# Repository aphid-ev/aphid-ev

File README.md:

# Aphid EV

Everything that goes into the electric conversion of a classic VW Beetle:
documentation, wiring, ECU hardware and firmware, and the desktop tooling to
manage it.

The documentation site at <https://bladlus.se> is built from [`site/`](site/)
and is the single source of truth for the project. READMEs in this repository
only say what a directory is and how to build it.

## Layout

| Path | What |
| --- | --- |
| [`site/`](site/) | Blog and wiki for bladlus.se, built with [aphid](https://aphid.lhelge.se) |
| [`wiring/`](wiring/) | Vehicle schematics and harness drawings, built with [wirebug](https://github.com/LHelge/wirebug) |
| [`crates/`](crates/) | Shared `no_std` Rust crates used by firmware and host code |
| [`ecus/`](ecus/) | One directory per ECU: KiCad hardware and Rust firmware side by side |
| [`apps/`](apps/) | Desktop application for managing the ECUs over CAN |
| [`tools/`](tools/) | Small host-side CLIs used by the build |

aphid and wirebug are developed in their own repositories; this repository
only uses them.

## Working in the repository

All tasks go through [`just`](https://just.systems). CI runs the same recipes.

```sh
just                  # list every recipe, including per-component modules
just host ci          # format, lint and test the host workspace
just vcm build        # build one ECU's firmware
just vcm export       # export one ECU's schematics for the site
just site serve       # live-reload the site
just docs             # generate all artifacts and build the site
just ci               # everything CI runs
```

Required tools: a Rust toolchain via rustup, `just`, `aphid`, `wirebug`,
KiCad 10 (`kicad-cli`) and `probe-rs` for flashing. `just install-aphid` and
`just install-wirebug` install the versions CI uses.

## Rust workspaces

The root `Cargo.toml` is the host workspace: everything that runs on a desktop,
plus the shared crates so their tests run on the host. Each firmware is its own
small workspace with its own target, linker script, profiles and lock file, and
depends on the shared crates by path.

## Releases

Components are versioned and tagged separately: `<component>-fw-vX.Y.Z` for
firmware, `<component>-hw-revX` for board revisions and `manager-vX.Y.Z` for
the desktop app.

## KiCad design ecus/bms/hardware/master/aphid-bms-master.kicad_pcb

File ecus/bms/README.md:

# BMS

Battery management system: one master and one slave board per battery module.

- `hardware/master/` — KiCad project for the master board.
- `hardware/slave/` — KiCad project for the slave board. It has no firmware.
- `firmware/` — embassy firmware for the master, a standalone cargo workspace.

Recipes: `just bms build | check | flash | erc | drc | export | ci`. The
hardware recipes cover both boards.

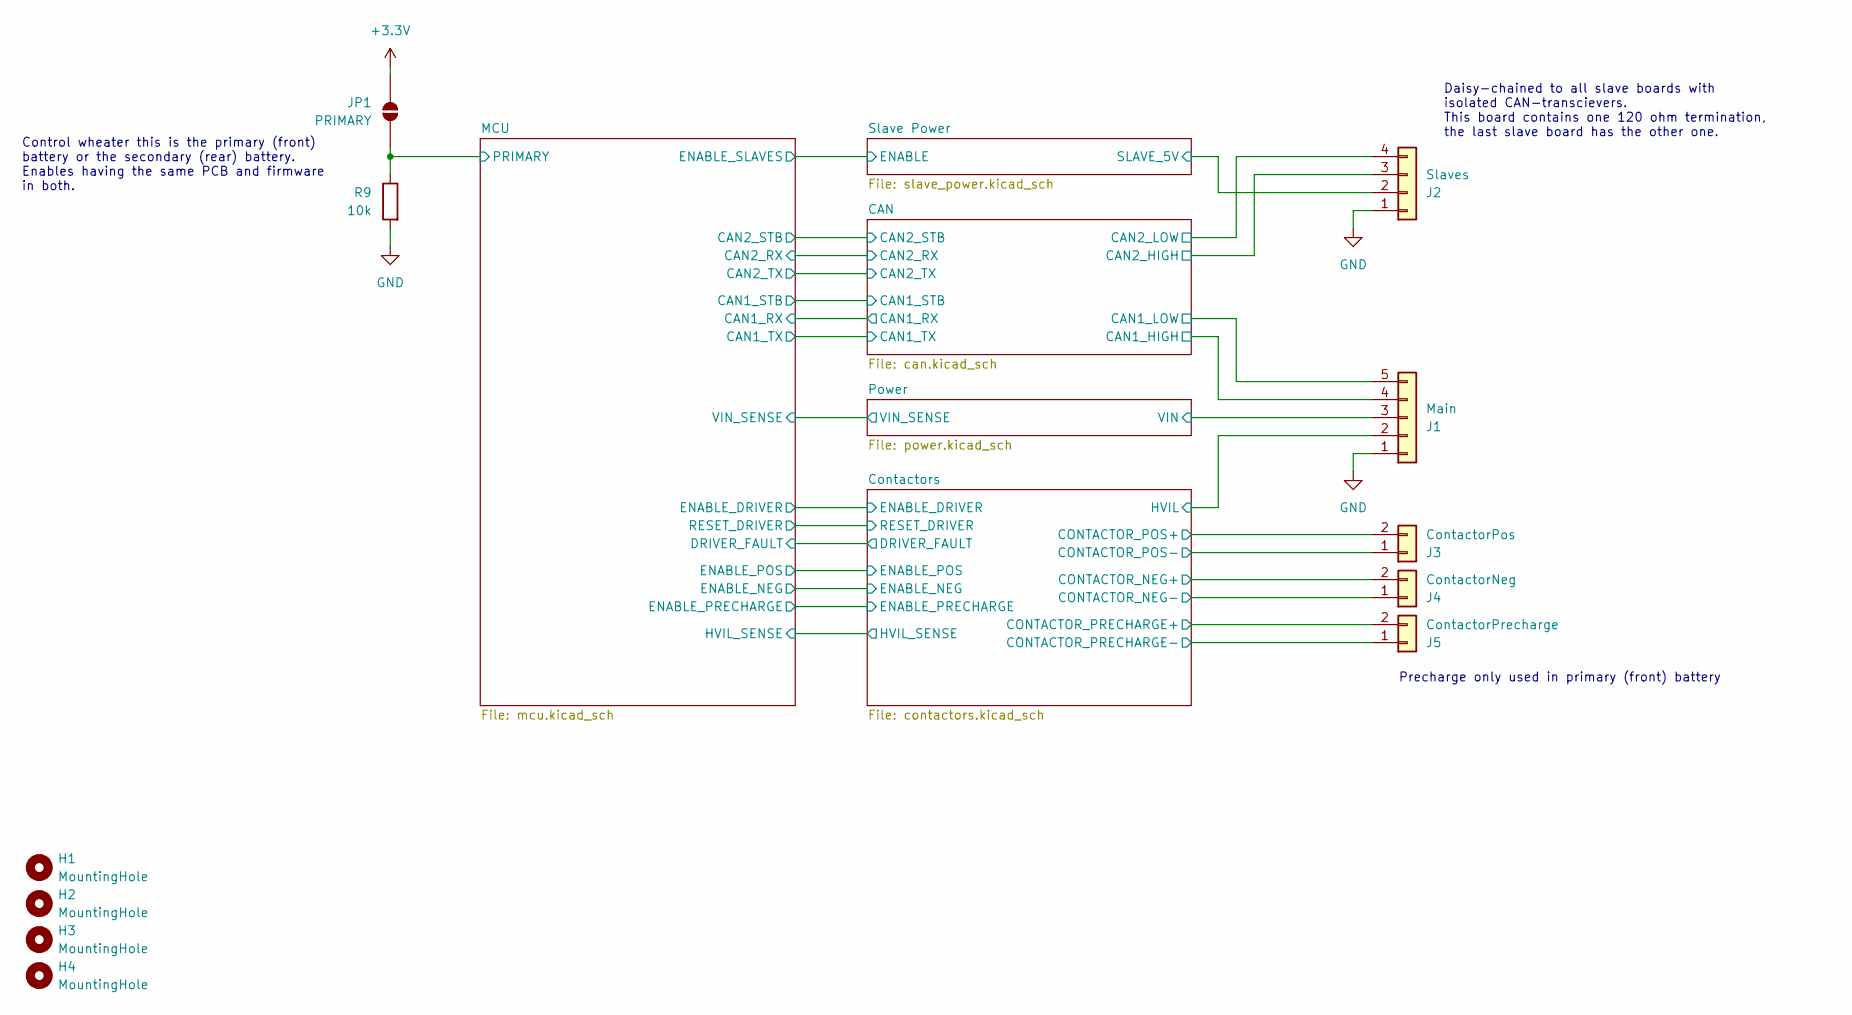
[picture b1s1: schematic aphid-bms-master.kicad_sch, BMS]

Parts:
H1, H2, H3, H4: MountingHole; MountingHole_4.3mm_M4
J1: Main; Molex_Micro-Fit_3.0_43650-0515_1x05_P3.00mm_Vertical
J2: Slaves; Molex_Micro-Fit_3.0_43045-0412_2x02_P3.00mm_Vertical
J3: ContactorPos; Molex_Micro-Fit_3.0_43650-0215_1x02_P3.00mm_Vertical
J4: ContactorNeg; Molex_Micro-Fit_3.0_43650-0215_1x02_P3.00mm_Vertical
J5: ContactorPrecharge; Molex_Micro-Fit_3.0_43650-0215_1x02_P3.00mm_Vertical
JP1: PRIMARY; SolderJumper-2_P1.3mm_Open_RoundedPad1.0x1.5mm
R9: 10k; R_0805_2012Metric

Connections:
+3.3V: JP1.2 (B); also elsewhere on the board
/CAN/CAN1_HIGH: J1.4; also elsewhere on the board
/CAN/CAN1_LOW: J1.5; also elsewhere on the board
/CAN/CAN2_HIGH: J2.3; also elsewhere on the board
/CAN/CAN2_LOW: J2.4; also elsewhere on the board
/Contactors/CONTACTOR_NEG-: J4.1; also elsewhere on the board
/Contactors/CONTACTOR_POS-: J3.1; also elsewhere on the board
/Contactors/CONTACTOR_PRECHARGE-: J5.1; also elsewhere on the board
/Contactors/HVIL: J1.2; also elsewhere on the board
/Contactors/HVIL_FILTERED: J3.2, J4.2, J5.2; also elsewhere on the board
/MCU/PRIMARY: JP1.1 (A), R9.1; also elsewhere on the board
/Power/VIN: J1.3; also elsewhere on the board
/Slave Power/SLAVE_5V: J2.2; also elsewhere on the board
GND: J1.1, J2.1, R9.2; also elsewhere on the board

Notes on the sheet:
Precharge only used in primary (front) battery
Control wheater this is the primary (front) battery or the secondary (rear) battery. Enables having the same PCB and firmware in both.
Daisy-chained to all slave boards with isolated CAN-transcievers. This board contains one 120 ohm termination, the last slave board has the other one.

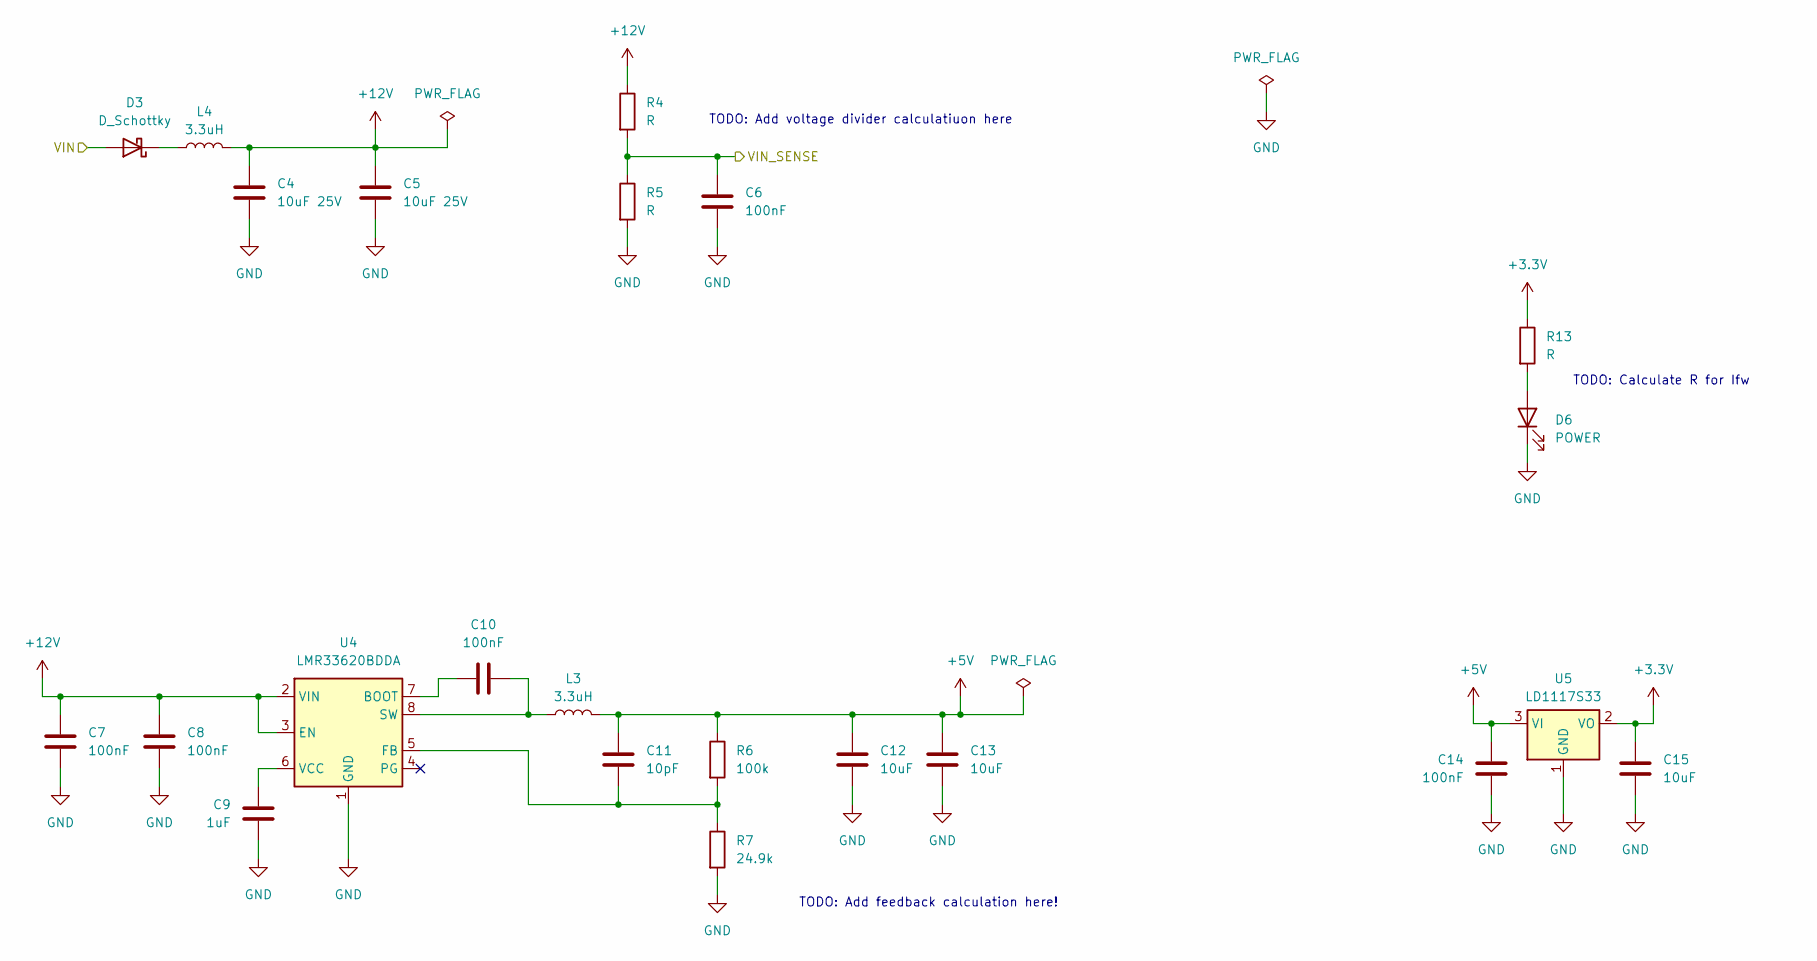
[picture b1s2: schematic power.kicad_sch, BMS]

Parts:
C4, C5: 10uF 25V; C_0805_2012Metric
C6, C14: 100nF; C_0805_2012Metric
C7, C8, C10: 100nF; C_0603_1608Metric
C9: 1uF; C_0603_1608Metric
C11: 10pF; C_0805_2012Metric
C12, C13, C15: 10uF; C_0805_2012Metric
D3: D_Schottky; D_SMC
D6: POWER; LED_0805_2012Metric
L3, L4: 3.3uH; L_Bourns_SRN8040TA
R4, R5, R13: R; R_0805_2012Metric
R6: 100k; R_0805_2012Metric
R7: 24.9k; R_0805_2012Metric
U4: LMR33620BDDA; Texas_HSOP-8-1EP_3.9x4.9mm_P1.27mm_ThermalVias
U5: LD1117S33; SOT-223-3_TabPin2

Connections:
+3.3V: C15.1, R13.1, U5.2 (VO); also elsewhere on the board
+5V: C11.1, C12.1, C13.1, C14.1, L3.2, R6.1, U5.3 (VI); also elsewhere on the board
+12V: C4.1, C5.1, C7.1, C8.1, L4.2, R4.1, U4.2 (VIN), U4.3 (EN)
/MCU/VIN_SENSE: C6.1, R4.2, R5.1; also elsewhere on the board
/Power/VIN: D3.2 (A); also elsewhere on the board
GND: C4.2, C5.2, C6.2, C7.2, C8.2, C9.2, C12.2, C13.2, C14.2, C15.2, D6.1 (K), R5.2, R7.2, U4.1 (GND), U4.9 (GND), U5.1 (GND); also elsewhere on the board
unnamed: D3.1 (K), L4.1
unnamed: D6.2 (A), R13.2
unnamed: C10.1, U4.7 (BOOT)
unnamed: C11.2, R6.2, R7.1, U4.5 (FB)
unnamed: C10.2, L3.1, U4.8 (SW)
unnamed: C9.1, U4.6 (VCC)

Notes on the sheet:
TODO: Calculate R for Ifw
TODO: Add feedback calculation here!
TODO: Add voltage divider calculatiuon here

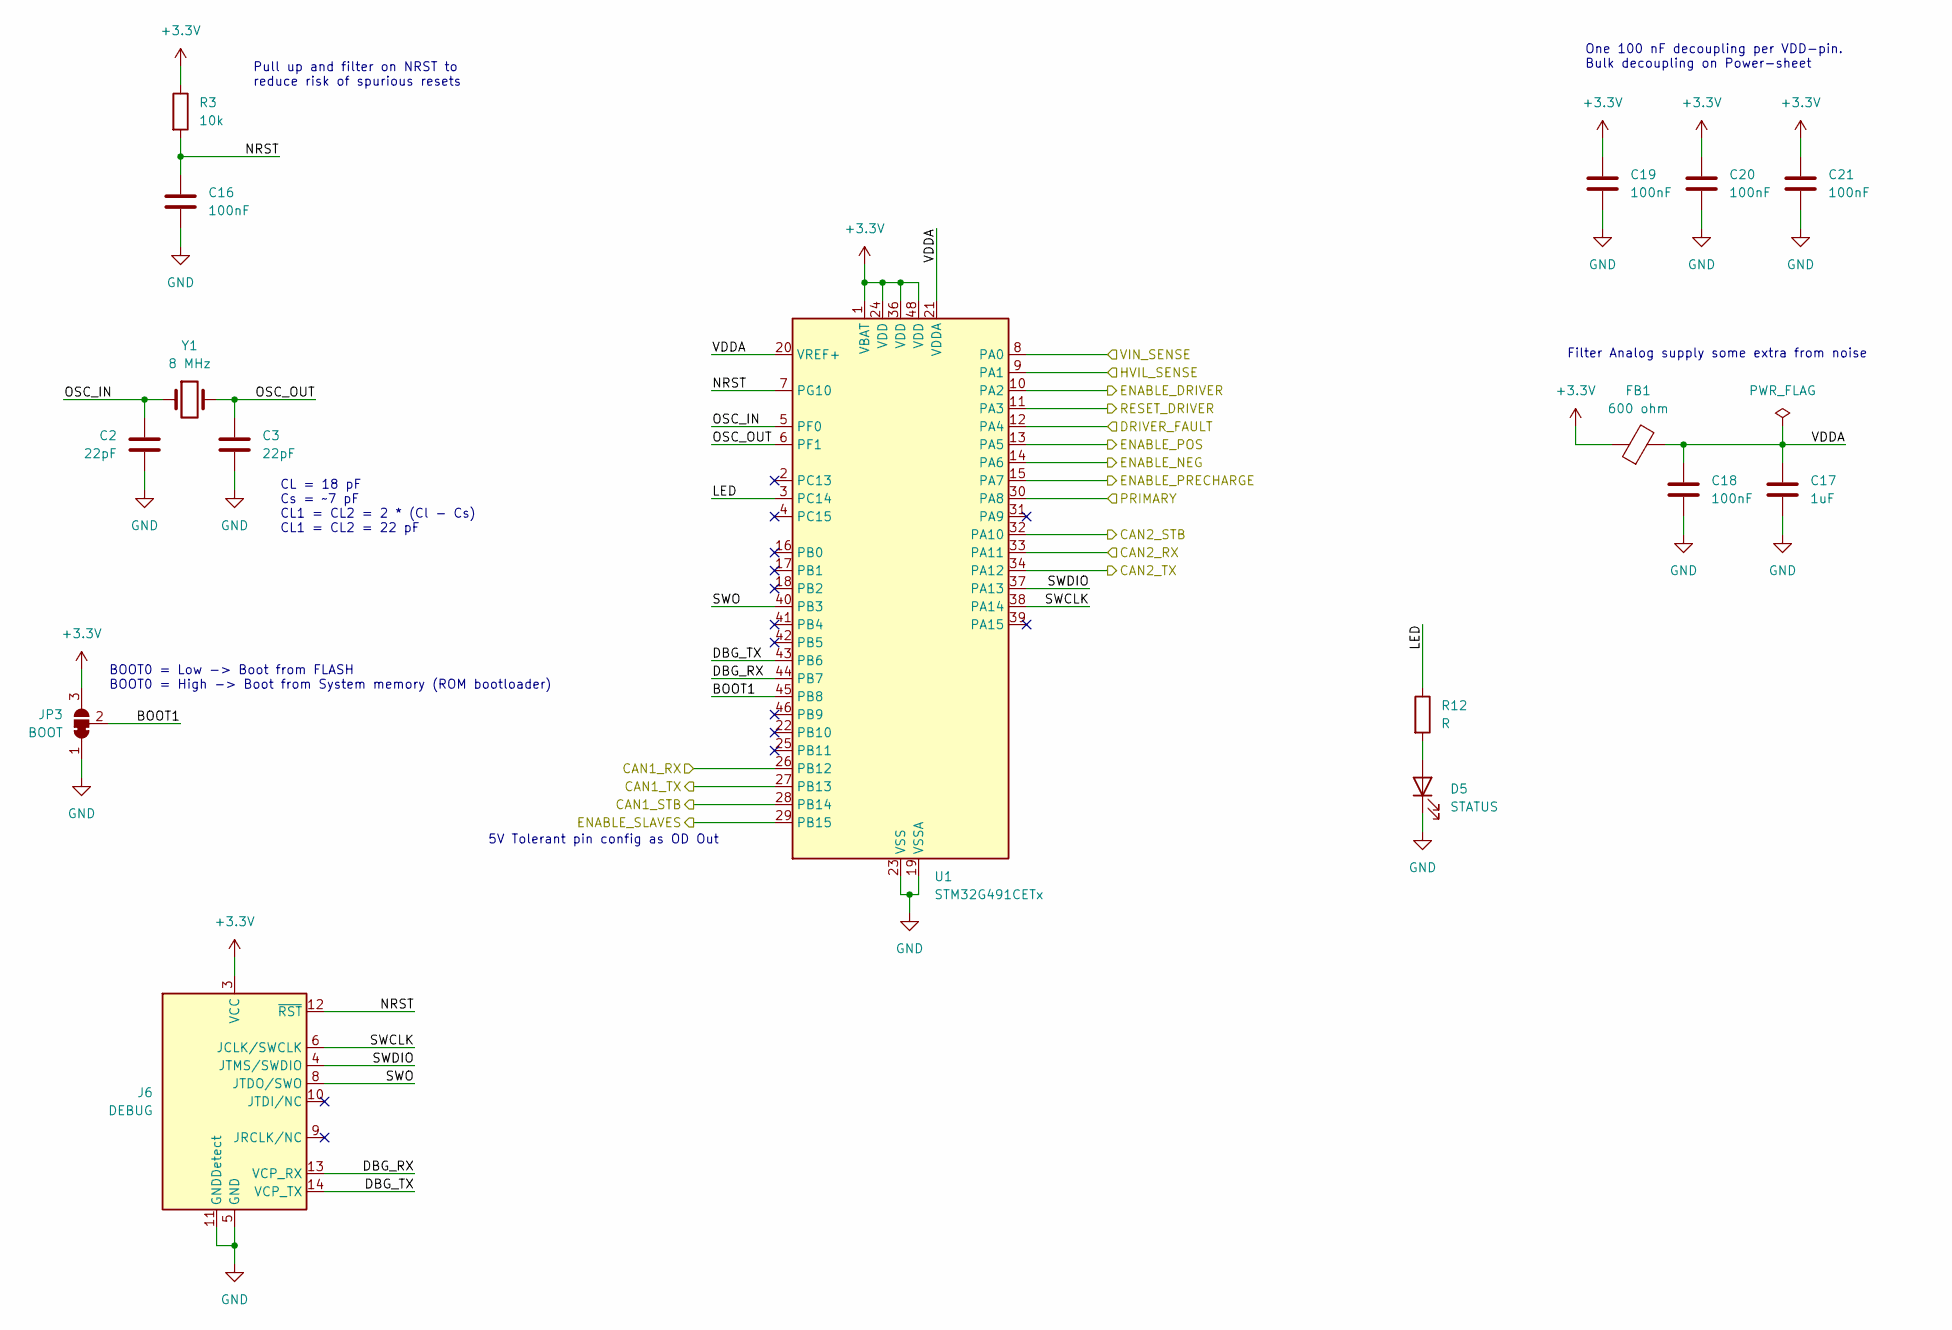
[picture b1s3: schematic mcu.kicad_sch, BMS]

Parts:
C2, C3: 22pF; C_0603_1608Metric
C16: 100nF; C_0805_2012Metric
C17: 1uF; C_0805_2012Metric
C18, C19, C20, C21: 100nF; C_0603_1608Metric
D5: STATUS; LED_0805_2012Metric
FB1: 600 ohm; L_0805_2012Metric
J6: DEBUG; PinHeader_2x07_P1.27mm_Vertical_SMD
JP3: BOOT; SolderJumper-3_P1.3mm_Bridged12_RoundedPad1.0x1.5mm_NumberL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
R3: 10k; R_0805_2012Metric
R12: R; R_0805_2012Metric
U1: STM32G491CETx; LQFP-48_7x7mm_P0.5mm
Y1: 8 MHz; ABM3-x.xxxMHZ-D2Y-T; Part ABM3-8.000MHZ-D2Y-T

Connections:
+3.3V: C19.1, C20.1, C21.1, FB1.1, J6.3 (VCC), JP3.3 (B), R3.1, U1.1 (VBAT), U1.24 (VDD), U1.36 (VDD), U1.48 (VDD); also elsewhere on the board
/CAN/CAN1_RX: U1.26 (PB12); also elsewhere on the board
/CAN/CAN1_STB: U1.28 (PB14); also elsewhere on the board
/CAN/CAN1_TX: U1.27 (PB13); also elsewhere on the board
/CAN/CAN2_RX: U1.33 (PA11); also elsewhere on the board
/CAN/CAN2_STB: U1.32 (PA10); also elsewhere on the board
/CAN/CAN2_TX: U1.34 (PA12); also elsewhere on the board
/Contactors/DRIVER_FAULT: U1.12 (PA4); also elsewhere on the board
/Contactors/ENABLE_DRIVER: U1.10 (PA2); also elsewhere on the board
/Contactors/ENABLE_NEG: U1.14 (PA6); also elsewhere on the board
/Contactors/ENABLE_POS: U1.13 (PA5); also elsewhere on the board
/Contactors/ENABLE_PRECHARGE: U1.15 (PA7); also elsewhere on the board
/Contactors/HVIL_SENSE: U1.9 (PA1); also elsewhere on the board
/Contactors/RESET_DRIVER: U1.11 (PA3); also elsewhere on the board
/MCU/BOOT1: JP3.2 (C), U1.45 (PB8)
/MCU/DBG_RX: J6.13 (VCP_RX), U1.44 (PB7)
/MCU/DBG_TX: J6.14 (VCP_TX), U1.43 (PB6)
/MCU/ENABLE_SLAVES: U1.29 (PB15); also elsewhere on the board
/MCU/LED: R12.1, U1.3 (PC14)
/MCU/NRST: C16.1, J6.12 (~RST), R3.2, U1.7 (PG10)
/MCU/OSC_IN: C2.1, U1.5 (PF0), Y1.1
/MCU/OSC_OUT: C3.1, U1.6 (PF1), Y1.2
/MCU/PRIMARY: U1.30 (PA8); also elsewhere on the board
/MCU/SWCLK: J6.6 (JCLK/SWCLK), U1.38 (PA14)
/MCU/SWDIO: J6.4 (JTMS/SWDIO), U1.37 (PA13)
/MCU/SWO: J6.8 (JTDO/SWO), U1.40 (PB3)
/MCU/VDDA: C17.1, C18.1, FB1.2, U1.20 (VREF+), U1.21 (VDDA)
/MCU/VIN_SENSE: U1.8 (PA0); also elsewhere on the board
GND: C2.2, C3.2, C16.2, C17.2, C18.2, C19.2, C20.2, C21.2, D5.1 (K), J6.5 (GND), J6.7 (GND), J6.11 (GNDDetect), JP3.1 (A), U1.19 (VSSA), U1.23 (VSS), U1.35 (VSS), U1.47 (VSS); also elsewhere on the board
unnamed: D5.2 (A), R12.2

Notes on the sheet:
CL = 18 pF Cs = ~7 pF CL1 = CL2 = 2 * (Cl - Cs) CL1 = CL2 = 22 pF
One 100 nF decoupling per VDD-pin. Bulk decoupling on Power-sheet
Pull up and filter on NRST to reduce risk of spurious resets
5V Tolerant pin config as OD Out
BOOT0 = Low -> Boot from FLASH BOOT0 = High -> Boot from System memory (ROM bootloader)
Filter Analog supply some extra from noise

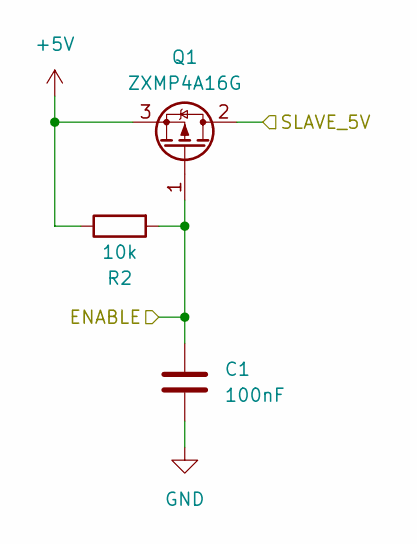
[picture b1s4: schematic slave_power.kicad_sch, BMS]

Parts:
C1: 100nF; C_0805_2012Metric
Q1: ZXMP4A16G; SOT-223-3_TabPin2
R2: 10k; R_0805_2012Metric

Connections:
+5V: Q1.3 (S), R2.1; also elsewhere on the board
/MCU/ENABLE_SLAVES: C1.1, Q1.1 (G), R2.2; also elsewhere on the board
/Slave Power/SLAVE_5V: Q1.2 (D); also elsewhere on the board
GND: C1.2; also elsewhere on the board

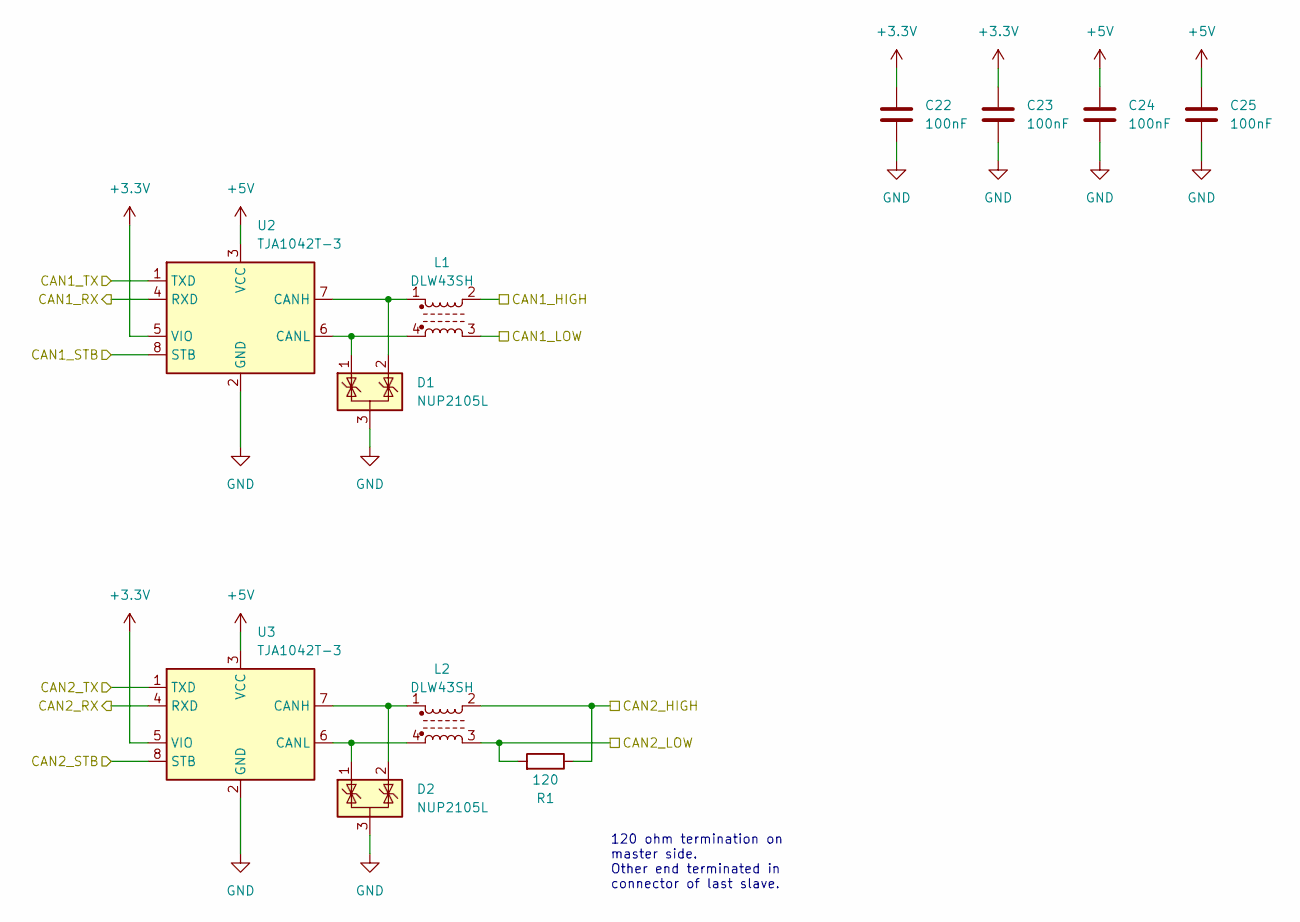
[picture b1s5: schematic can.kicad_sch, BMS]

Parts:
C22, C23, C24, C25: 100nF; C_0603_1608Metric
D1, D2: NUP2105L; SOT-23
L1, L2: DLW43SH
R1: 120; R_0805_2012Metric
U2, U3: TJA1042T-3; SOIC-8_3.9x4.9mm_P1.27mm

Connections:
+3.3V: C22.1, C23.1, U2.5 (VIO), U3.5 (VIO); also elsewhere on the board
+5V: C24.1, C25.1, U2.3 (VCC), U3.3 (VCC); also elsewhere on the board
/CAN/CAN1_HIGH: L1.2; also elsewhere on the board
/CAN/CAN1_LOW: L1.3; also elsewhere on the board
/CAN/CAN1_RX: U2.4 (RXD); also elsewhere on the board
/CAN/CAN1_STB: U2.8 (STB); also elsewhere on the board
/CAN/CAN1_TX: U2.1 (TXD); also elsewhere on the board
/CAN/CAN2_HIGH: L2.2, R1.1; also elsewhere on the board
/CAN/CAN2_LOW: L2.3, R1.2; also elsewhere on the board
/CAN/CAN2_RX: U3.4 (RXD); also elsewhere on the board
/CAN/CAN2_STB: U3.8 (STB); also elsewhere on the board
/CAN/CAN2_TX: U3.1 (TXD); also elsewhere on the board
GND: C22.2, C23.2, C24.2, C25.2, D1.3 (A), D2.3 (A), U2.2 (GND), U3.2 (GND); also elsewhere on the board
unnamed: D1.2 (K), L1.1, U2.7 (CANH)
unnamed: D1.1 (K), L1.4, U2.6 (CANL)
unnamed: D2.2 (K), L2.1, U3.7 (CANH)
unnamed: D2.1 (K), L2.4, U3.6 (CANL)

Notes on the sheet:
120 ohm termination on master side. Other end terminated in connector of last slave.

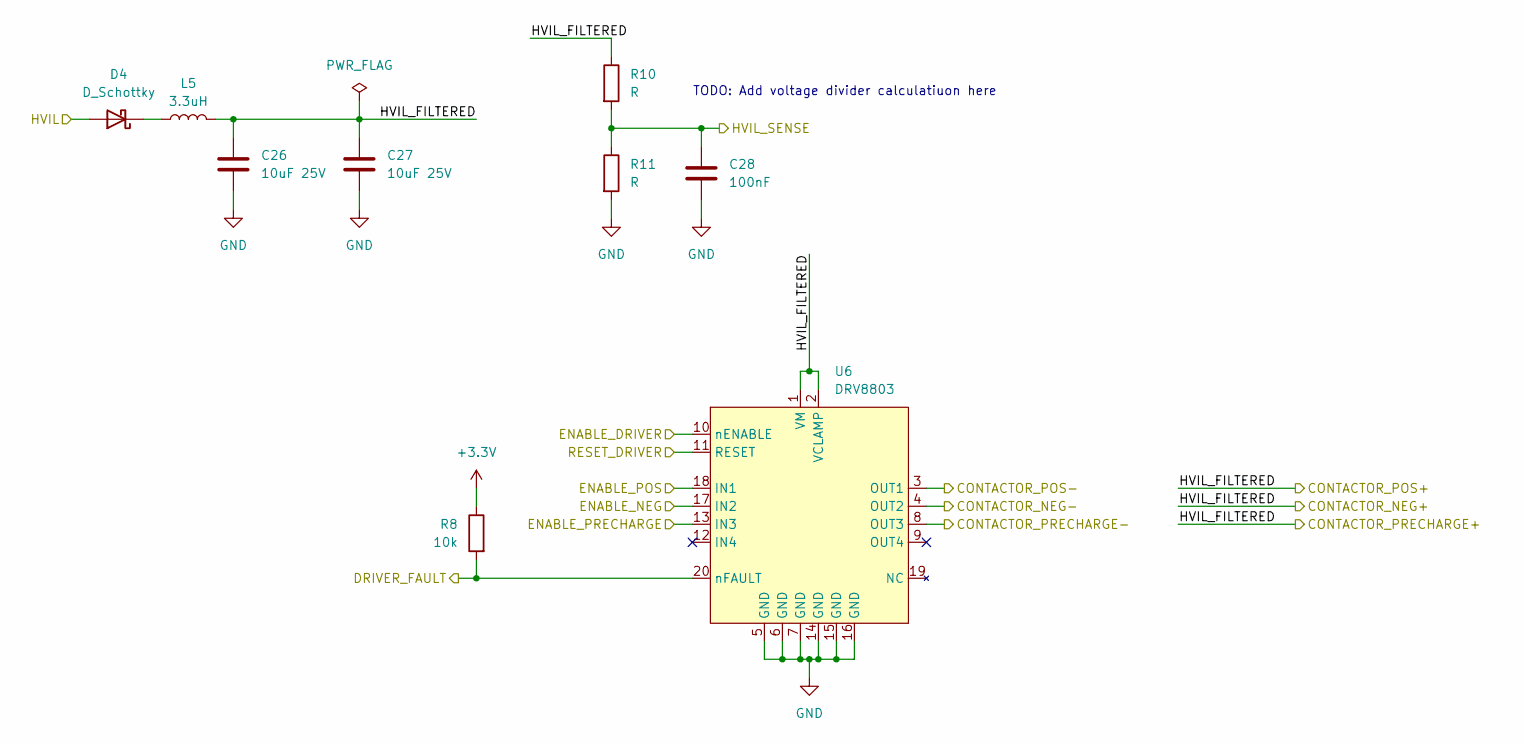
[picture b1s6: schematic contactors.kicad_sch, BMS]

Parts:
C26, C27: 10uF 25V; C_0805_2012Metric
C28: 100nF; C_0805_2012Metric
D4: D_Schottky; D_SMC
L5: 3.3uH; L_Bourns_SRN8040TA
R8: 10k; R_0805_2012Metric
R10, R11: R; R_0805_2012Metric
U6: DRV8803; SOIC-20W_7.5x12.8mm_P1.27mm

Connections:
+3.3V: R8.1; also elsewhere on the board
/Contactors/CONTACTOR_NEG-: U6.4 (OUT2); also elsewhere on the board
/Contactors/CONTACTOR_POS-: U6.3 (OUT1); also elsewhere on the board
/Contactors/CONTACTOR_PRECHARGE-: U6.8 (OUT3); also elsewhere on the board
/Contactors/DRIVER_FAULT: R8.2, U6.20 (nFAULT); also elsewhere on the board
/Contactors/ENABLE_DRIVER: U6.10 (nENABLE); also elsewhere on the board
/Contactors/ENABLE_NEG: U6.17 (IN2); also elsewhere on the board
/Contactors/ENABLE_POS: U6.18 (IN1); also elsewhere on the board
/Contactors/ENABLE_PRECHARGE: U6.13 (IN3); also elsewhere on the board
/Contactors/HVIL: D4.2 (A); also elsewhere on the board
/Contactors/HVIL_FILTERED: C26.1, C27.1, L5.2, R10.1, U6.1 (VM), U6.2 (VCLAMP); also elsewhere on the board
/Contactors/HVIL_SENSE: C28.1, R10.2, R11.1; also elsewhere on the board
/Contactors/RESET_DRIVER: U6.11 (RESET); also elsewhere on the board
GND: C26.2, C27.2, C28.2, R11.2, U6.5 (GND), U6.6 (GND), U6.7 (GND), U6.14 (GND), U6.15 (GND), U6.16 (GND); also elsewhere on the board
unnamed: D4.1 (K), L5.1

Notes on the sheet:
TODO: Add voltage divider calculatiuon here

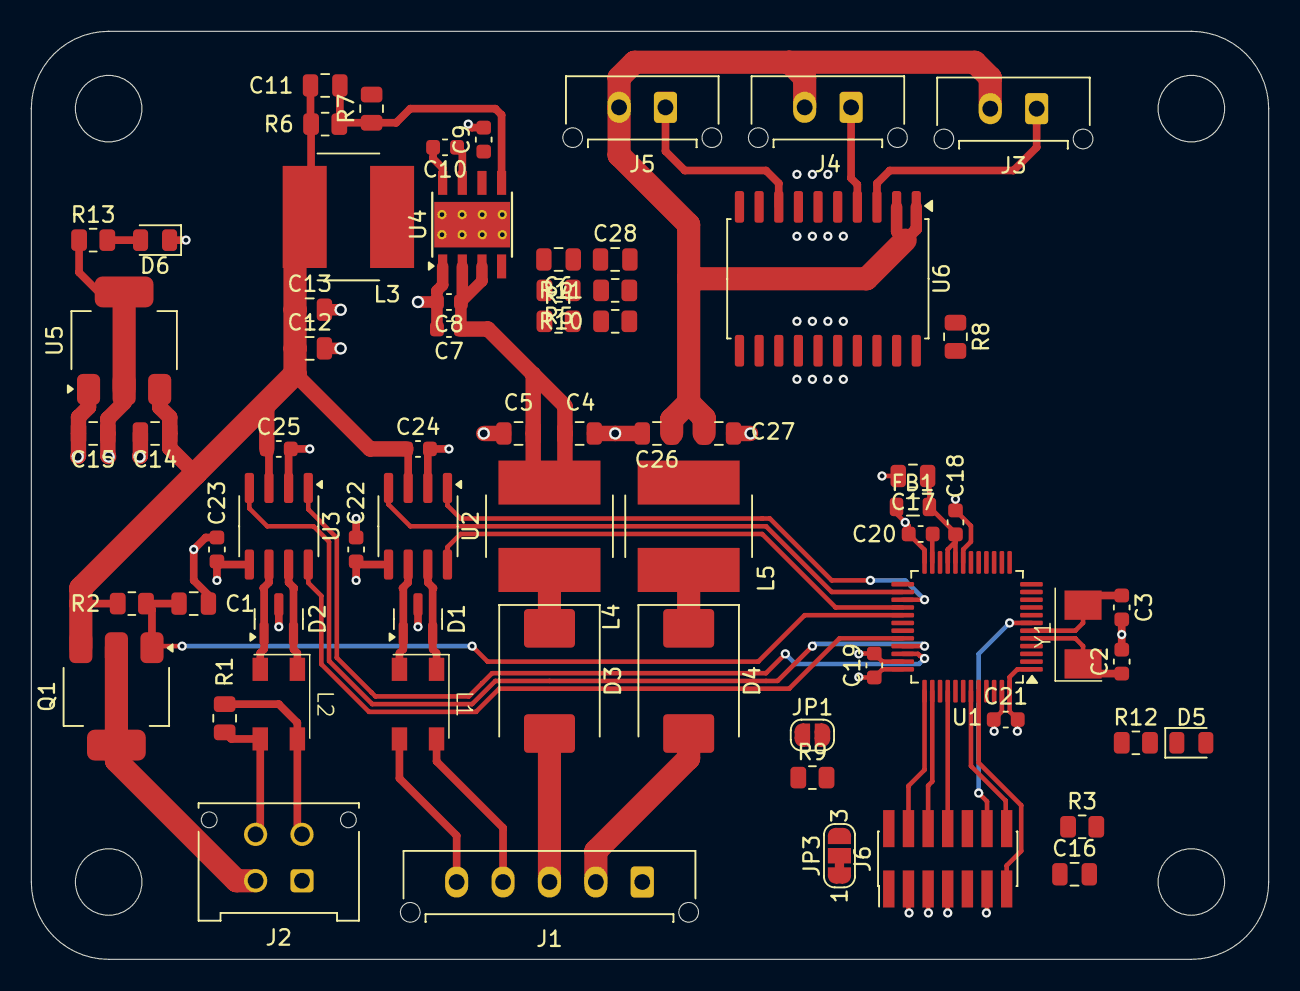
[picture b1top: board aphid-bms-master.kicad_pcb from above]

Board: 4 copper layers, 80.0 x 60.0 mm, 73 parts (0 on the bottom side), 54 nets.

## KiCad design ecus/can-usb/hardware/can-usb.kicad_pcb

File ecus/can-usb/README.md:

# CAN/USB interface

USB adapter for talking to the vehicle's CAN bus from a computer. See
[the wiki page](https://bladlus.se/wiki/can-usb/) for how it works.

- `hardware/` — KiCad project for the board.
- `firmware/` — embassy firmware for the STM32G431CB, a standalone cargo
  workspace. It supports `can-usb-hw-revA` only, the board in `hardware/`.
  Pins: USB on PA11/PA12, FDCAN1 on PB8/PB9, transceiver standby on PC13,
  LEDs RX on PA7, TX on PA6 and ERR on PA5, with a 16 MHz crystal. They are
  named in `firmware/src/board.rs` and nowhere else.
- `host/` — host-side USB library, a member of the host workspace, used by
  the manager app. It also builds `can-usb`, a test CLI.
- `host/70-can-usb.rules` — udev rule for access without root on Linux.

Recipes: `just can-usb build | check | flash | erc | drc | export | ci`. The
host library is built and tested by `just host ci`.

```sh
cargo run -p can-usb-host -- info        # protocol and firmware version, serial
cargo run -p can-usb-host -- listen      # print every frame on the bus
cargo run -p can-usb-host -- ping        # send a frame every 5 s, print the reply
cargo run -p can-usb-host -- throughput  # stream --count frames, print rate and losses
cargo run -p can-usb-host -- listen --bitrate 250 --mode listen-only
```

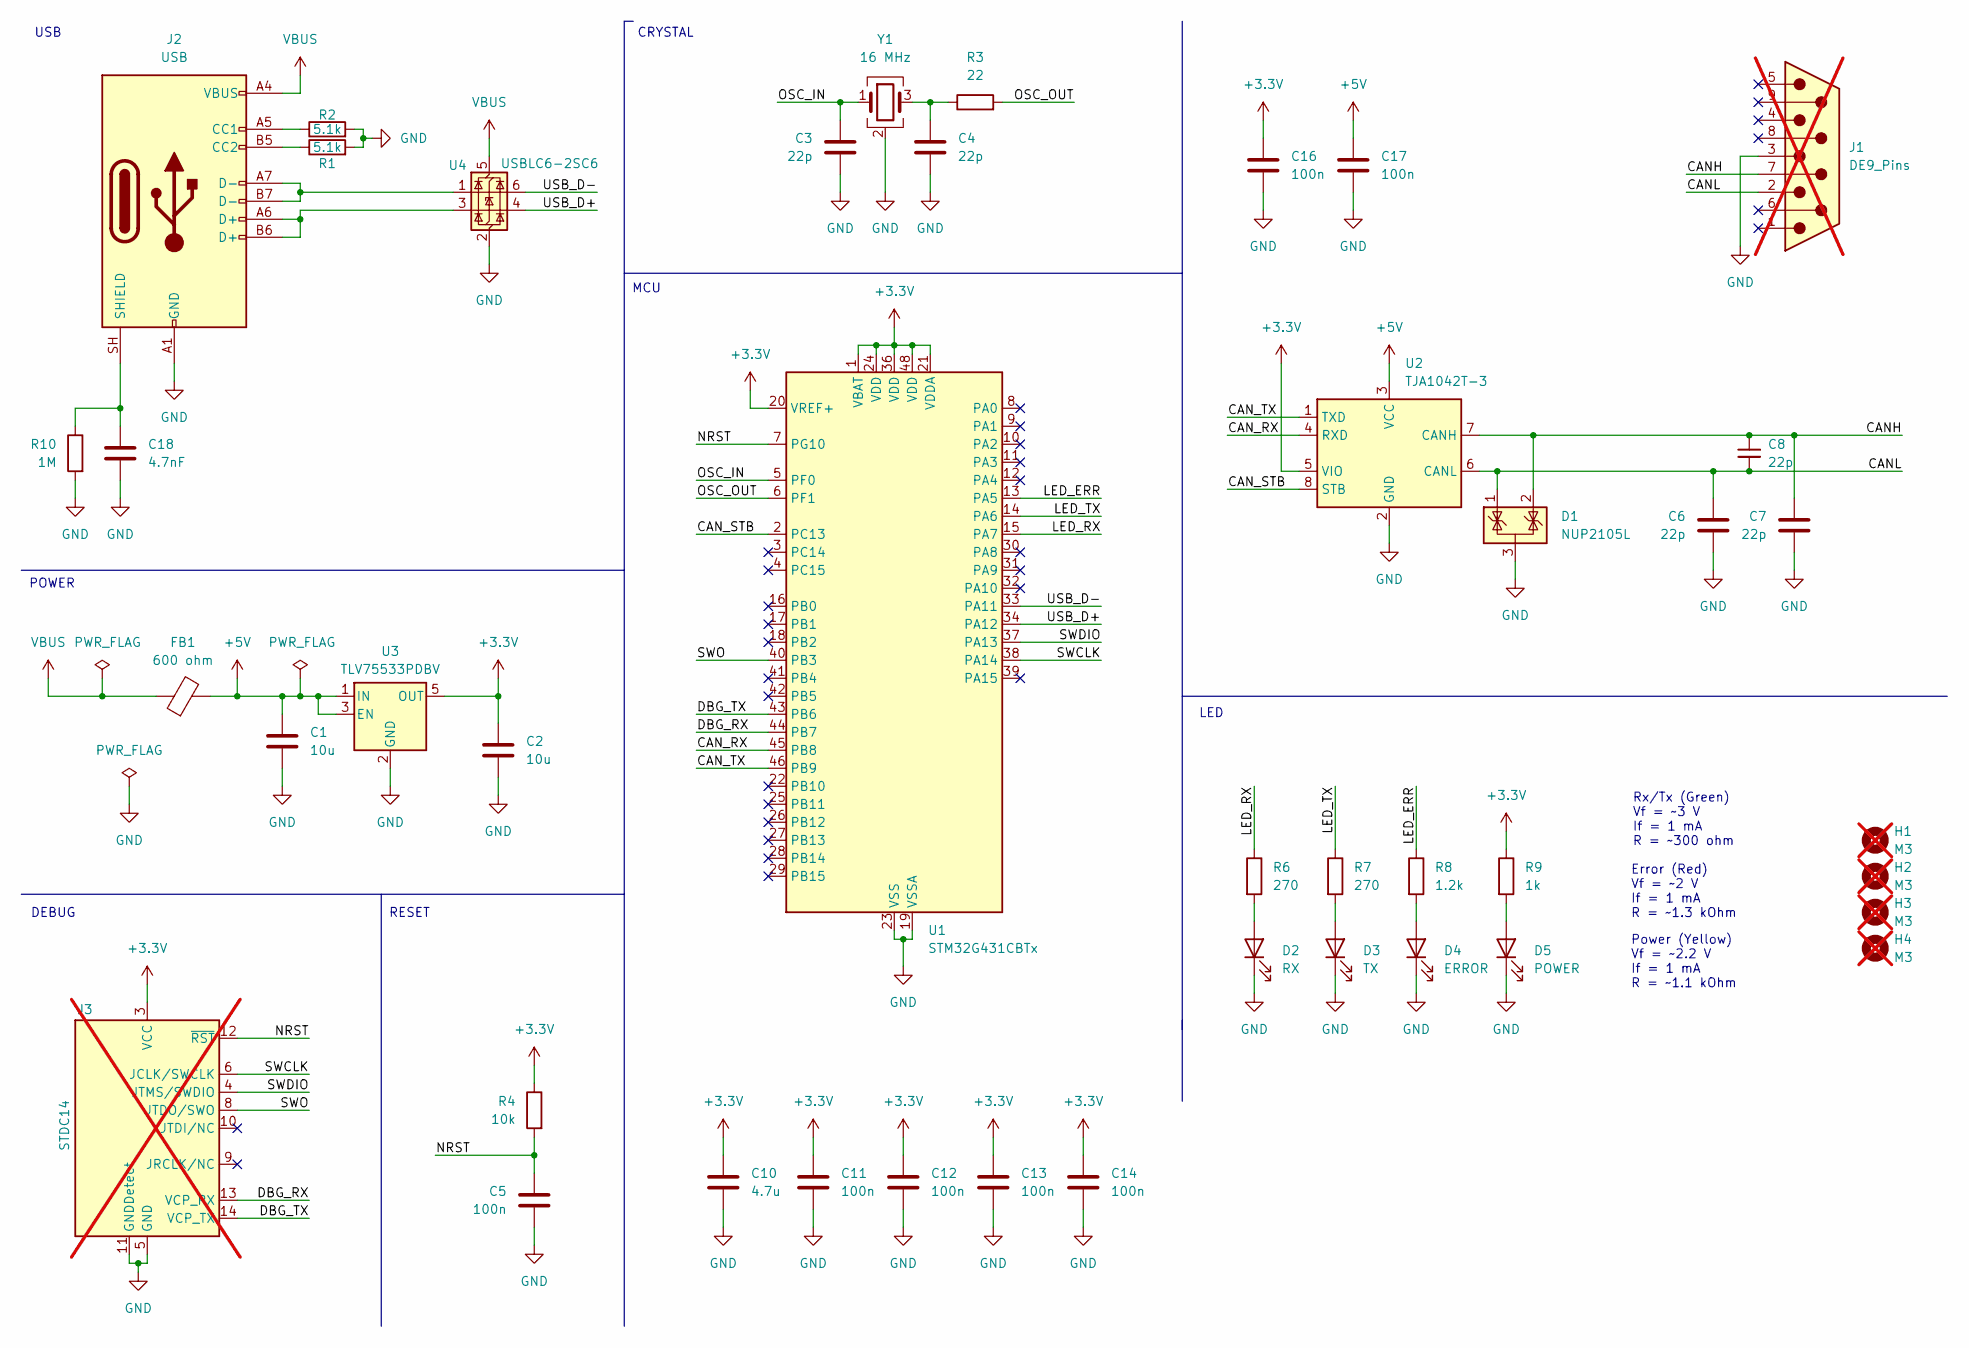
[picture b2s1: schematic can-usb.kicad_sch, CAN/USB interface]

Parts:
C1, C2: 10u; C_0603_1608Metric; JLCPCB C19702
C3, C4: 22p; C_0402_1005Metric; JLCPCB C1555
C5: 100n; C_0603_1608Metric; JLCPCB C14663
C6, C7, C8: 22p; C_0603_1608Metric; JLCPCB C1653
C10: 4.7u; C_0603_1608Metric; JLCPCB C19666
C11, C12, C13, C14, C16, C17: 100n; C_0402_1005Metric; JLCPCB C1525
C18: 4.7nF; C_0603_1608Metric; JLCPCB C53987
D1: NUP2105L; SOT-23; JLCPCB C14486
D2: RX; LED_0805_2012Metric; JLCPCB C2297
D3: TX; LED_0805_2012Metric; JLCPCB C2297
D4: ERROR; LED_0805_2012Metric; JLCPCB C84256
D5: POWER; LED_0805_2012Metric; JLCPCB C2296
FB1: 600 ohm; L_0603_1608Metric; JLCPCB C1002
H1, H2, H3, H4: M3; MountingHole_3.2mm_M3; not fitted
J1: DE9_Pins; DSUB-9_Pins_EdgeMount_P2.77mm; not fitted
J2: USB; USB_C_Receptacle_HRO_TYPE-C-31-M-12; JLCPCB C165948
J3: STDC14; PinHeader_2x07_P1.27mm_Vertical_SMD; not fitted
R1, R2: 5.1k; R_0603_1608Metric; JLCPCB C23186
R3: 22; R_0402_1005Metric; JLCPCB C25092
R4: 10k; R_0603_1608Metric; JLCPCB C25804
R6, R7: 270; R_0603_1608Metric; JLCPCB C22966
R8: 1.2k; R_0603_1608Metric; JLCPCB 0603
R9: 1k; R_0603_1608Metric; JLCPCB C21190
R10: 1M; R_0603_1608Metric; JLCPCB C22935
U1: STM32G431CBTx; LQFP-48_7x7mm_P0.5mm; JLCPCB C529355
U2: TJA1042T-3; SOIC-8_3.9x4.9mm_P1.27mm; JLCPCB C132227
U3: TLV75533PDBV; SOT-23-5; JLCPCB C404027
U4: USBLC6-2SC6; SOT-23-6; JLCPCB C7519
Y1: 16 MHz; Crystal_SMD_3225-4Pin_3.2x2.5mm; JLCPCB C13738

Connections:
+3.3V: C2.1, C10.1, C11.1, C12.1, C13.1, C14.1, C16.1, J3.3 (VCC), R4.1, R9.1, U1.1 (VBAT), U1.20 (VREF+), U1.21 (VDDA), U1.24 (VDD), U1.36 (VDD), U1.48 (VDD), U2.5 (VIO), U3.5 (OUT)
+5V: C1.1, C17.1, FB1.2, U2.3 (VCC), U3.1 (IN), U3.3 (EN)
/CANH: C7.1, C8.1, D1.2 (K), J1.7, U2.7 (CANH)
/CANL: C6.1, C8.2, D1.1 (K), J1.2, U2.6 (CANL)
/CAN_RX: U1.45 (PB8), U2.4 (RXD)
/CAN_STB: U1.2 (PC13), U2.8 (STB)
/CAN_TX: U1.46 (PB9), U2.1 (TXD)
/DBG_RX: J3.13 (VCP_RX), U1.44 (PB7)
/DBG_TX: J3.14 (VCP_TX), U1.43 (PB6)
/LED_ERR: R8.1, U1.13 (PA5)
/LED_RX: R6.1, U1.15 (PA7)
/LED_TX: R7.1, U1.14 (PA6)
/NRST: C5.1, J3.12 (~RST), R4.2, U1.7 (PG10)
/OSC_IN: C3.1, U1.5 (PF0), Y1.1
/OSC_OUT: R3.2, U1.6 (PF1)
/SWCLK: J3.6 (JCLK/SWCLK), U1.38 (PA14)
/SWDIO: J3.4 (JTMS/SWDIO), U1.37 (PA13)
/SWO: J3.8 (JTDO/SWO), U1.40 (PB3)
/USB_D+: U1.34 (PA12), U4.4 (I/O2)
/USB_D-: U1.33 (PA11), U4.6 (I/O1)
GND: C1.2, C2.2, C3.2, C4.2, C5.2, C6.2, C7.2, C10.2, C11.2, C12.2, C13.2, C14.2, C16.2, C17.2, C18.2, D1.3 (A), D2.1 (K), D3.1 (K), D4.1 (K), D5.1 (K), J1.3, J2.A1 (GND), J2.A12 (GND), J2.B1 (GND), J2.B12 (GND), J3.5 (GND), J3.7 (GND), J3.11 (GNDDetect), R1.2, R2.2, R10.2, U1.19 (VSSA), U1.23 (VSS), U1.35 (VSS), U1.47 (VSS), U2.2 (GND), U3.2 (GND), U4.2 (GND), Y1.2 (G), Y1.4 (G)
unnamed: C4.1, R3.1, Y1.3
unnamed: D2.2 (A), R6.2
unnamed: D3.2 (A), R7.2
unnamed: D4.2 (A), R8.2
unnamed: D5.2 (A), R9.2
unnamed: J2.A5 (CC1), R2.1
unnamed: J2.B5 (CC2), R1.1
unnamed: J2.A6 (D+), J2.B6 (D+), U4.3 (I/O2)
unnamed: J2.A7 (D-), J2.B7 (D-), U4.1 (I/O1)
unnamed: C18.1, J2.SH (SHIELD), R10.1
VBUS: FB1.1, J2.A4 (VBUS), J2.A9 (VBUS), J2.B4 (VBUS), J2.B9 (VBUS), U4.5 (VBUS)

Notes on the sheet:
DEBUG
Error (Red) Vf = ~2 V If = 1 mA R = ~1.3 kOhm
LED
MCU
CRYSTAL
Rx/Tx (Green) Vf = ~3 V If = 1 mA R = ~300 ohm
Power (Yellow) Vf = ~2.2 V If = 1 mA R = ~1.1 kOhm
POWER
RESET
USB

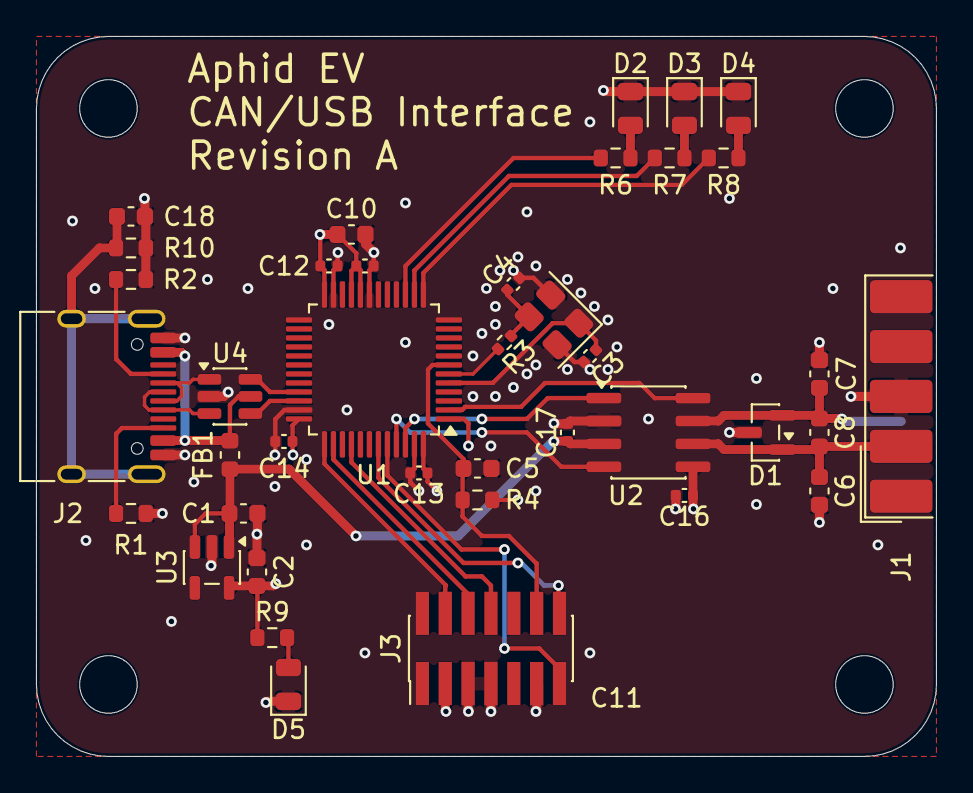
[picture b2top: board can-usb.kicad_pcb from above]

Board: 4 copper layers, 50.0 x 40.0 mm, 43 parts (0 on the bottom side), 32 nets.
